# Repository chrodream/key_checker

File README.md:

# Key Checker

## Overview

​	・Know the lock status of each room by HTTP communication between the primary device(Raspberry Pi) and the secondary device(ESP32).
​	・See in the log when the door was locked or unlocked.

## Environment

​	・Raspberry Pi
​	・ESP32 Devkit-C 32D/E

## Parts list

### Primary (Raspberry Pi)

| Products                                         | Quantity |
| ------------------------------------------------ | -------- |
| Raspberry Pi                                     | 1        |
| micro SD Card(Limit to 32GB if you use 32bit OS) | 1        |

### Secondary (ESP32)

| Products                                                     | KiCAD assign   | Quantity (per each) |
| ------------------------------------------------------------ | -------------- | ------------------- |
| [ESP32-DevkitC-32](https://akizukidenshi.com/catalog/g/gM-15673/) | U1             | 1                   |
| [0.96inch OLED](https://akizukidenshi.com/catalog/g/gP-12031/) | U2             | 1                   |
| 3mm Power LED (No specification)                             | D1             | 1                   |
| [5mm RGB LED](https://www.marutsu.co.jp/pc/i/1356696/)       | D2             | 1                   |
| [30kΩ Semi-fixed resistance](https://akizukidenshi.com/catalog/g/gP-14907/) | RV1            | 1                   |
| 470Ω Chip-resistor                                           | R1, R2, R3, R4 | 4                   |
| 10kΩ Chip-resistor                                           | R5, R6, R7     | 3                   |
| [Micro switch](https://akizukidenshi.com/catalog/g/gP-14659/) | SW1            | 1                   |
| [Illumination sensor ](https://akizukidenshi.com/catalog/g/gI-02325/) | Q1             | 1                   |
| 3-Pin socket                                                 | J1, J2         | 2                   |
| 3-line wire                                                  |                | 1                   |

## Usage

1. Launch key_server.py on Raspberry Pi 
   e.g. `python3 ~/key_checker/key_server.py`
2. upload client_esp.ino to ESP32.
   **Notice: Please change Wi-Fi's SSID, Password and Room number.**
3. Sends a HTTP data per 10 seconds when ESP is connected to Power supply.

## Trouble-shooting

| Error Code      | Response method                                              |
| --------------- | ------------------------------------------------------------ |
| -1              | Maybe Network configuration is wrong. Please check IP-address, Subnet mask, DNS and Home Gate Way's address are correct. |
| -11             | Please do not launch on SSH.                                 |
| 3-digits number | It's HTTP response code.                                     |

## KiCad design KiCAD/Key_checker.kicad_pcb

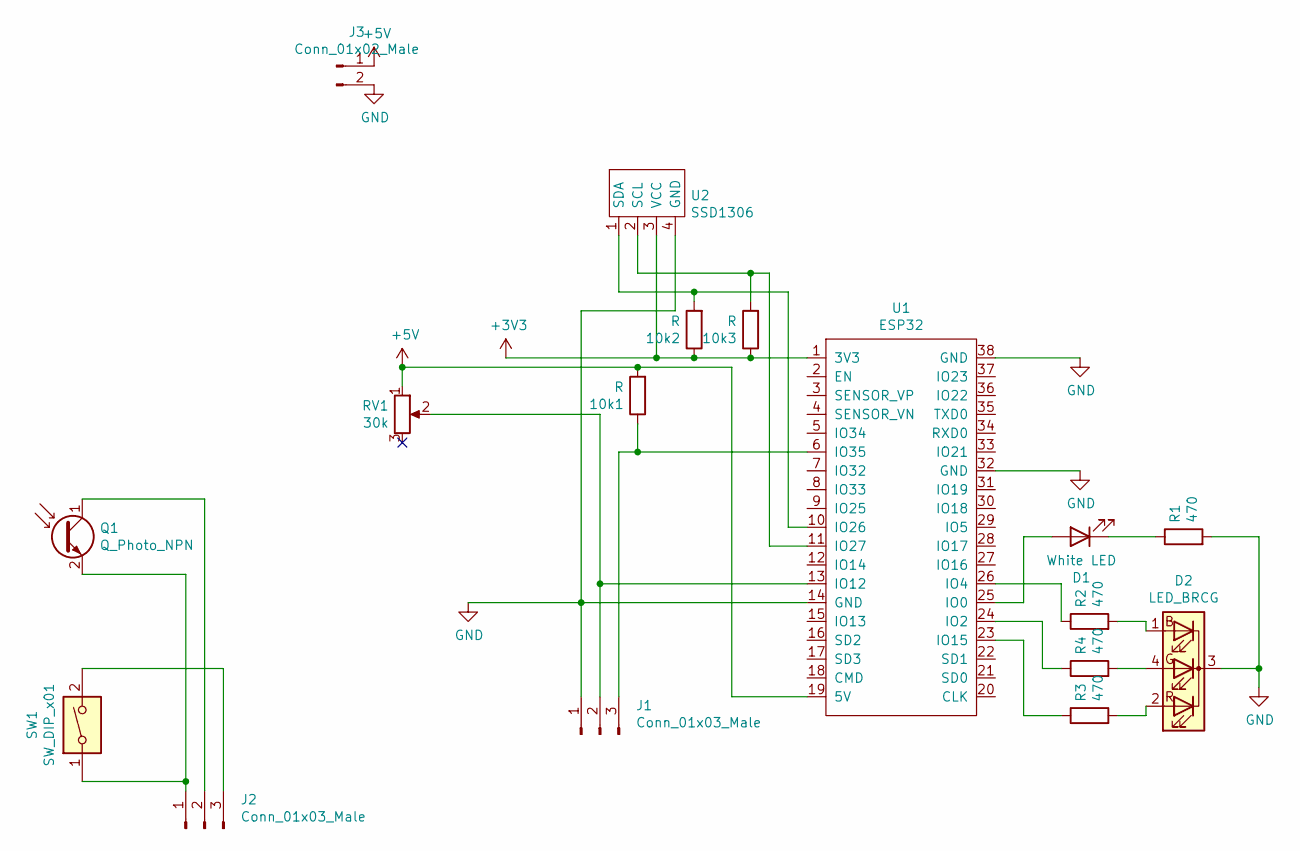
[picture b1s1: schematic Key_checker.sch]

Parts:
10k1, 10k2, 10k3: R; R_0603_1608Metric_Pad0.98x0.95mm_HandSolder
D1: White LED; LED_D3.0mm
D2: LED_BRCG; LED_D5.0mm-4_RGB
J1, J2: Conn_01x03_Male; PinHeader_1x03_P2.54mm_Horizontal
J3: Conn_01x02_Male; PinHeader_1x02_P2.54mm_Horizontal
Q1: Q_Photo_NPN; LED_D5.0mm
R1, R2, R3, R4: 470; R_0603_1608Metric_Pad0.98x0.95mm_HandSolder
RV1: 30k; Potentiometer_ACP_CA6-H2,5_Horizontal
SW1: SW_DIP_x01; SS-10GL
U1: ESP32; DIP-38_1000_ELL
U2: SSD1306; PinHeader_1x04_P2.54mm_Vertical

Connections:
+3V3: 10k2.1, 10k3.1, U1.1 (3V3), U2.3 (VCC)
+5V: 10k1.2, J3.1, RV1.1, U1.19 (5V)
GND: D2.3 (K), J1.1, J3.2, R1.2, U1.14 (GND), U1.32 (GND), U1.38 (GND), U2.4 (GND)
unnamed: 10k1.1, J1.3, U1.6 (IO35)
unnamed: 10k2.2, U1.10 (IO26), U2.1 (SDA)
unnamed: 10k3.2, U1.11 (IO27), U2.2 (SCL)
unnamed: D1.1 (K), R1.1
unnamed: D1.2 (A), U1.25 (IO0)
unnamed: D2.1 (BA), R2.2
unnamed: D2.2 (RA), R3.2
unnamed: D2.4 (GA), R4.2
unnamed: J1.2, RV1.2, U1.13 (IO12)
unnamed: J2.1, Q1.2 (E), SW1.1
unnamed: J2.2, Q1.1 (C)
unnamed: J2.3, SW1.2
unnamed: R2.1, U1.26 (IO4)
unnamed: R3.1, U1.23 (IO15)
unnamed: R4.1, U1.24 (IO2)

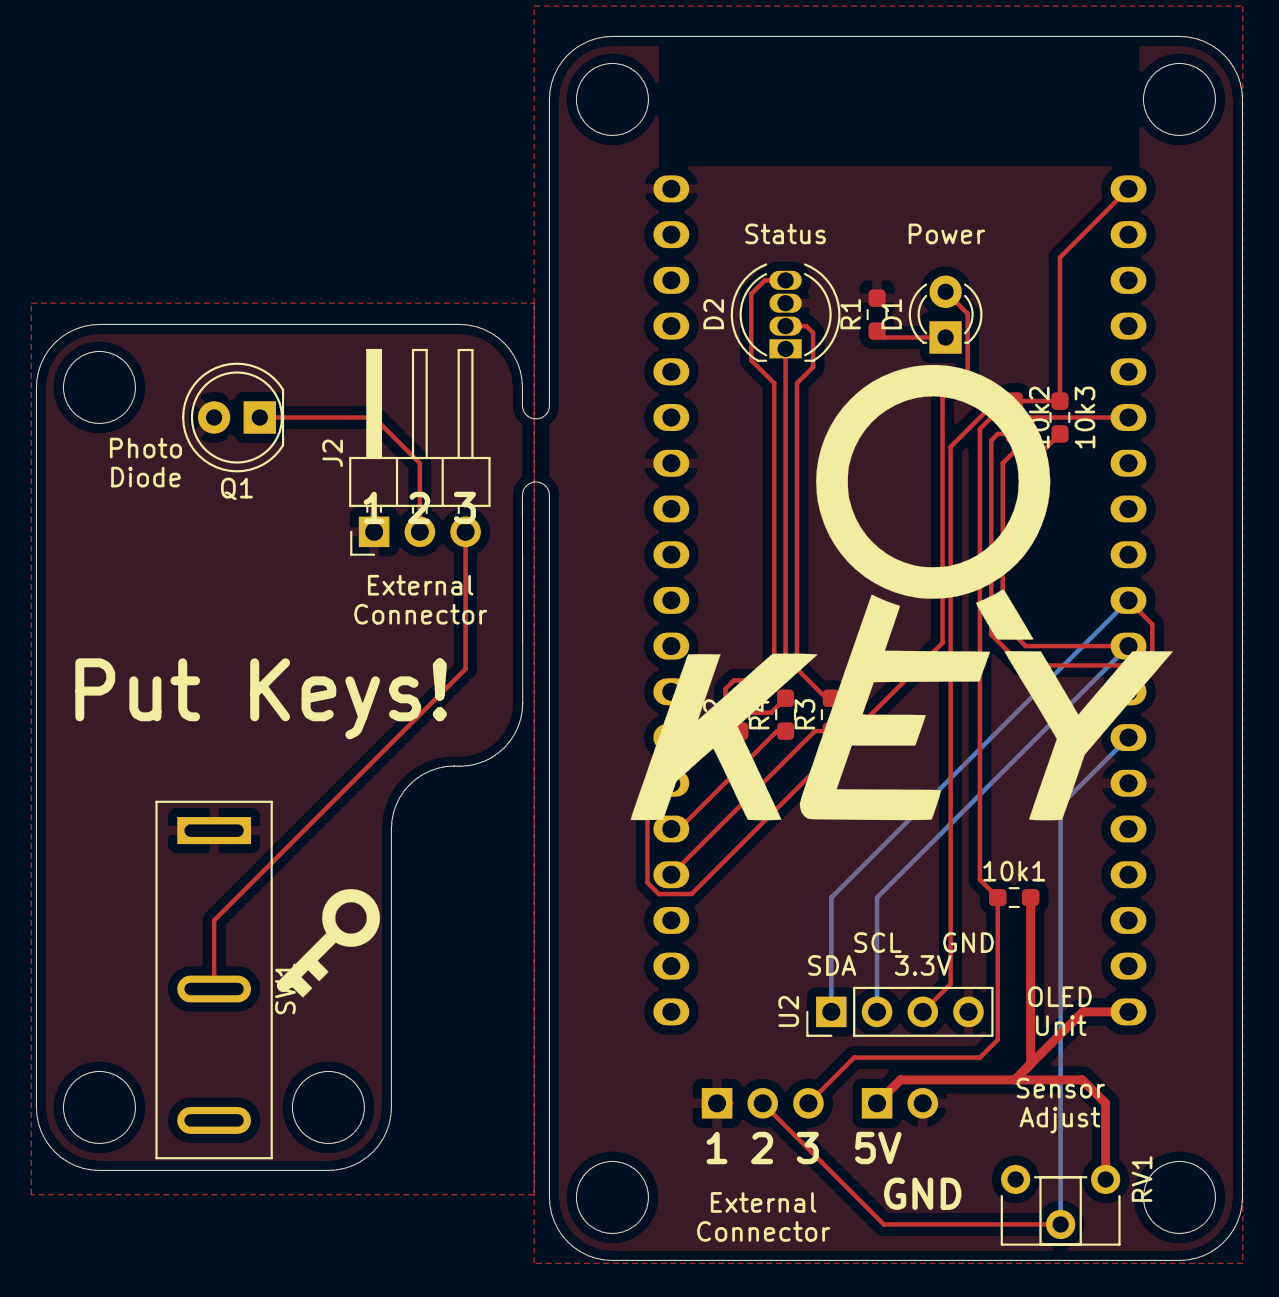
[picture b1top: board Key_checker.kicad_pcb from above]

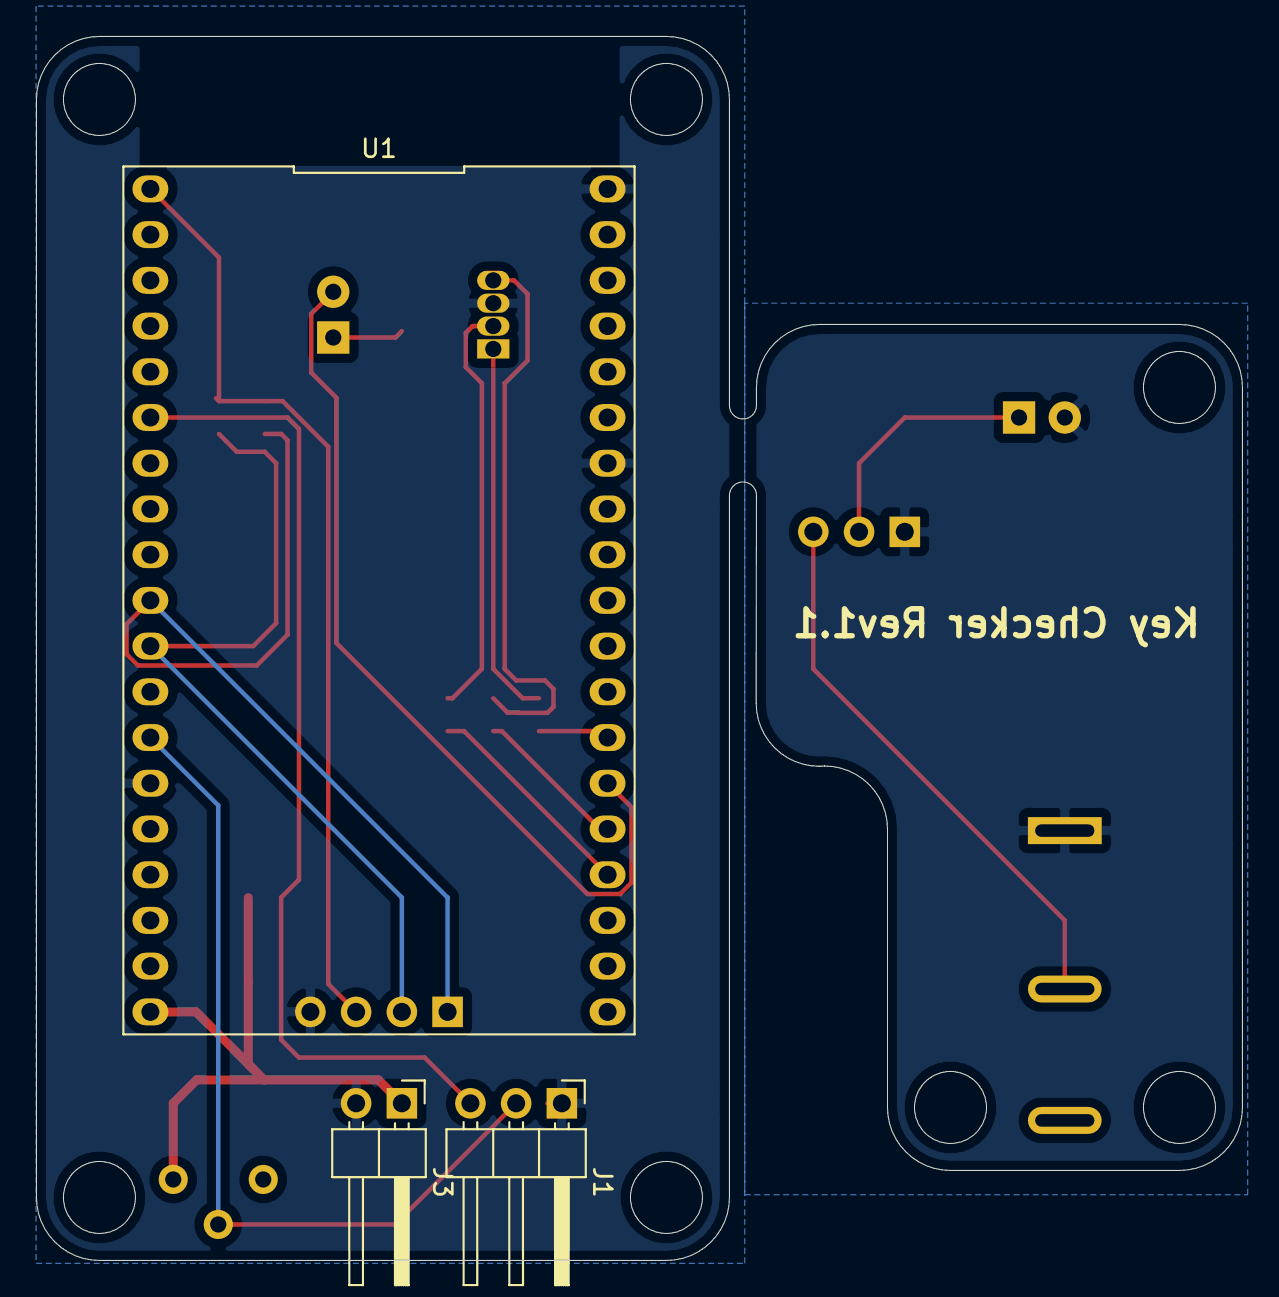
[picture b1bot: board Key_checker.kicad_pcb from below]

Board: 2 copper layers, 67.0 x 68.0 mm, 17 parts (3 on the bottom side), 18 nets.

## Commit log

2021-04-23 created server file in python
2021-05-07 Added README.md
2021-05-07 Changed README.md
2021-05-14 fixed WiFi.h bug
2021-05-21 Enabled static IP address
2021-05-28 Changed to HTTP server style
2021-06-01 Added writing from key_server.py data to roomlog.csv
2021-06-11 fix server and ESP's Wi-Fi bug, added key and light Sensor
2021-06-22 Added GUI mode
2021-06-25 added OLED mode, fix some bug
2021-06-25 Add PCB data
2021-07-02 fix some bugs
2021-07-02 nothing spectial
2021-07-02 Key Checker's PCB is Completed!
2021-07-02 Deleted posttest.ino
2021-07-09 Key Checker is available now!
2021-07-09 Fixed problem in PCB
2021-07-09 Rename README_EN.md to README.md
2021-07-09 fix markdown
2021-07-16 fixed ui on key_server.py
2021-07-16 fixed PCB
2021-12-03 PCB is changed
2021-12-14 Prepare for M5Paper
2021-12-17 Modified PCB
2021-12-24 key status is added on webpage
2022-01-11 Add auto-reload, more easy to see CUI
2022-01-13 add display update time
2022-01-13 add checksum function
2022-01-17 Change color orange if key is locked and light is on
2022-01-20 add checksum for ESP32
2022-01-21 fix bug in client_esp.ino and add gui.html
